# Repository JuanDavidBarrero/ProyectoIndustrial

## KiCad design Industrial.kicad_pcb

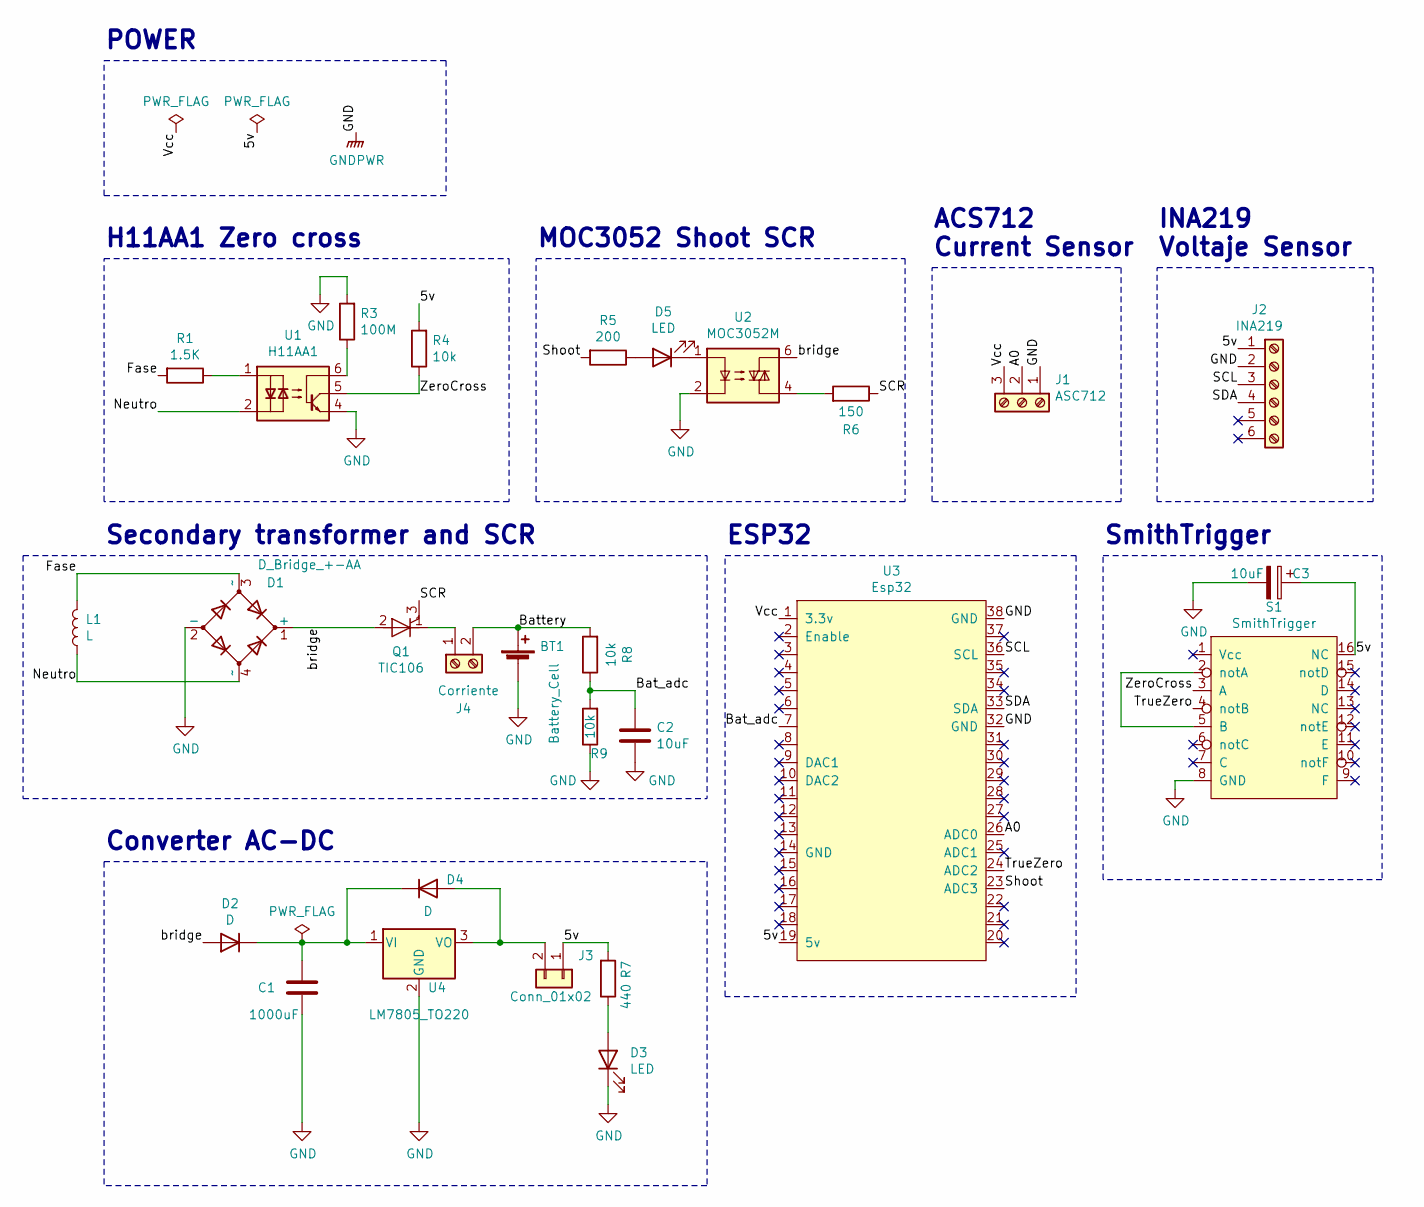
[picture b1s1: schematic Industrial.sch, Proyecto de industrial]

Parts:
BT1: Battery_Cell; TerminalBlock_bornier-2_P5.08mm
C1: 1000uF; CP_Radial_D13.0mm_P5.00mm
C2, C3: 10uF; CP_Radial_D5.0mm_P2.50mm
D1: D_Bridge_+-AA; Diode_Bridge_Round_D9.0mm
D2, D4: D; D_A-405_P7.62mm_Horizontal
D3, D5: LED; LED_D4.0mm
J1: ASC712; PinSocket_1x03_P2.54mm_Vertical
J2: INA219; PinSocket_1x06_P2.54mm_Vertical
J3: Conn_01x02; PinHeader_1x02_P2.54mm_Vertical
J4: Corriente; TerminalBlock_bornier-2_P5.08mm
L1: L; TerminalBlock_bornier-2_P5.08mm
Q1: TIC106; TerminalBlock_bornier-3_P5.08mm
R1: 1.5K; R_Axial_DIN0309_L9.0mm_D3.2mm_P5.08mm_Vertical
R3: 100M; R_Axial_DIN0309_L9.0mm_D3.2mm_P5.08mm_Vertical
R4, R8, R9: 10k; R_Axial_DIN0309_L9.0mm_D3.2mm_P5.08mm_Vertical
R5: 200; R_Axial_DIN0309_L9.0mm_D3.2mm_P5.08mm_Vertical
R6: 150; R_Axial_DIN0309_L9.0mm_D3.2mm_P5.08mm_Vertical
R7: 440; R_Axial_DIN0309_L9.0mm_D3.2mm_P5.08mm_Vertical
S1: SmithTrigger; DIP-16_W7.62mm_LongPads
U1: H11AA1; DIP-6_W7.62mm_LongPads
U2: MOC3052M; DIP-6_W7.62mm_LongPads
U3: Esp32; ESP32
U4: LM7805_TO220; TO-220-3_Vertical

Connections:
/5v: C3.1, J2.1, J3.1, R4.2, R7.2, S1.16 (NC), U3.19 (5v)
/A0: J1.2, U3.26 (ADC0)
/Bat_adc: C2.1, R8.1, R9.2, U3.7
/Battery: BT1.1 (+), J4.2, R8.2
/Fase: D1.3 (~~), L1.1, R1.2
/Neutro: D1.4 (~~), L1.2, U1.2
/SCL: J2.3, U3.36 (SCL)
/SCR: Q1.3 (G), R6.1
/SDA: J2.4, U3.33 (SDA)
/Shoot: R5.2, U3.23 (ADC3)
/TrueZero: S1.4 (notB), U3.24 (ADC2)
/Vcc: J1.3, U3.1 (3.3v)
/ZeroCross: R4.1, S1.3 (A), U1.5
/bridge: D1.1 (+), D2.2 (A), Q1.2 (A), U2.6
GND: BT1.2 (-), C1.2, C2.2, C3.2, D1.2 (-), D3.1 (K), J1.1, J2.2, R3.2, R9.1, S1.8 (GND), U1.4, U2.2, U3.32 (GND), U3.38 (GND), U4.2 (GND)
unnamed: C1.1, D2.1 (K), D4.1 (K), U4.1 (VI)
unnamed: D3.2 (A), R7.1
unnamed: D4.2 (A), J3.2, U4.3 (VO)
unnamed: D5.1 (K), U2.1
unnamed: D5.2 (A), R5.1
unnamed: J4.1, Q1.1 (K)
unnamed: R1.1, U1.1
unnamed: R3.1, U1.6
unnamed: R6.2, U2.4
unnamed: S1.2 (notA), S1.5 (B)

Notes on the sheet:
POWER
H11AA1 Zero cross
MOC3052 Shoot SCR
ACS712 Current Sensor
INA219 Voltaje Sensor
Secondary transformer and SCR
ESP32
SmithTrigger
Converter AC-DC

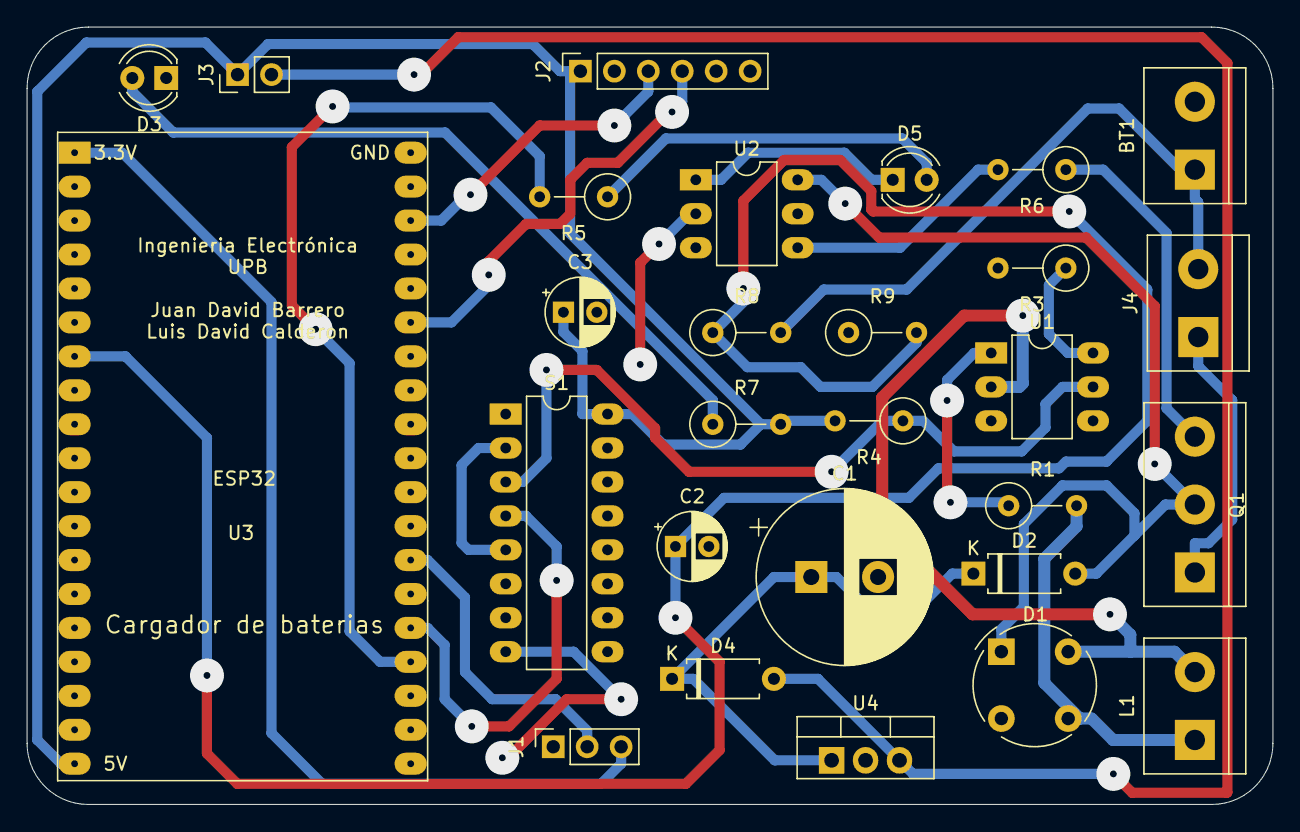
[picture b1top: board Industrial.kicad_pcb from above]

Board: 2 copper layers, 93.2 x 58.2 mm, 28 parts (0 on the bottom side), 25 nets.

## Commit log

2021-04-11 Finish conecctions
2021-04-11 Netlist generated and pcd start
2021-04-12 fix pcb
2021-04-12 about to route
2021-04-13 finish first version
2021-04-13 add rectifier start new desing
2021-04-13 finish but it can be better
2021-04-14 final desing with adc pin 24
